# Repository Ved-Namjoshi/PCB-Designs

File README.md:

# PCB Designs – Embedded & Electronics Hardware

This repository contains PCB designs created using KiCad for embedded
and electronics hardware projects.

## Projects
- Tiny Solar Power Supply
- LMR51450 Buck Converter
- LED Torch Circuit
- Breadboard Power Supply

## Author
Ved Namjoshi

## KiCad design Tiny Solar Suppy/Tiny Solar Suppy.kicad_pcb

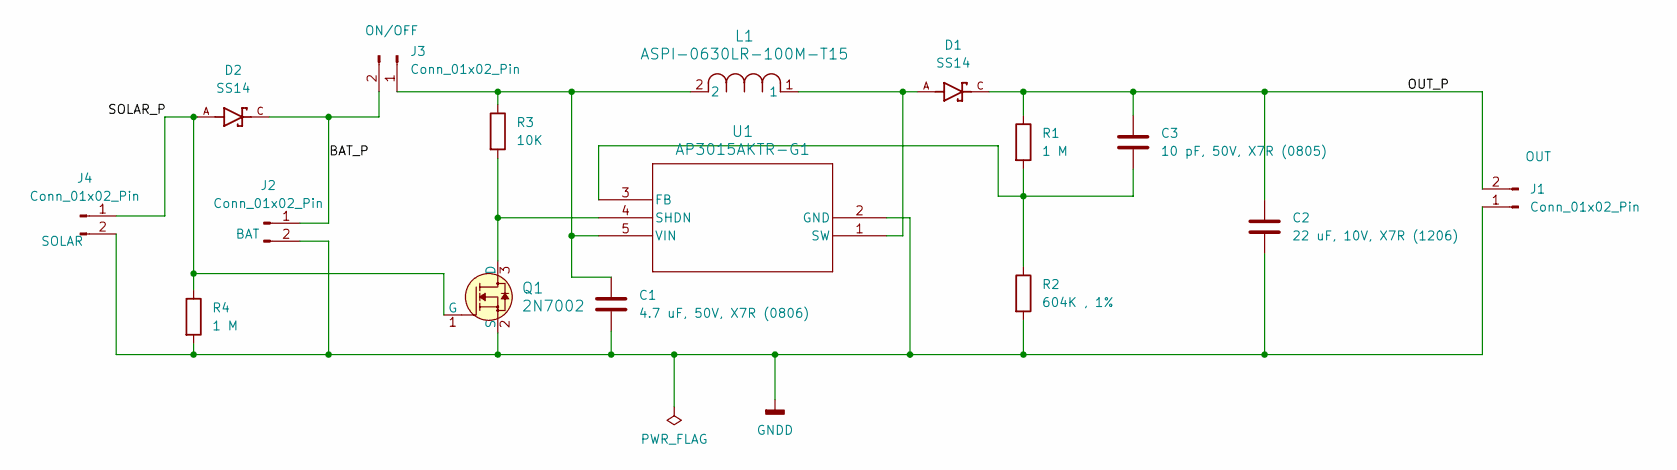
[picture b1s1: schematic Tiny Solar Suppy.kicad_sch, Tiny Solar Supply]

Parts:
C1: 4.7 uF, 50V, X7R (0806); C_0805_2012Metric
C2: 22 uF, 10V, X7R (1206); C_1206_3216Metric
C3: 10 pF, 50V, X7R (0805); C_0805_2012Metric
D1, D2: SS14; DIOM4325X250N; PARTREV O2102
J1, J2, J3: Conn_01x02_Pin; PinHeader_1x02_P2.54mm_Vertical
J4: Conn_01x02_Pin; PinHeader_1x02_P2.54mm_Horizontal
L1: ASPI-0630LR-100M-T15; IND_ASPI-0630LR_ABR
Q1: 2N7002; SOT-23-3; MPN 2N7002; Digi-Key_PN 2N7002NCT-ND
R1, R4: 1 M; R_0805_2012Metric
R2: 604K , 1%; R_0805_2012Metric
R3: 10K; R_0805_2012Metric
U1: AP3015AKTR-G1; SOT23-5_1P55X2P9_DIO

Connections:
/BAT_P: D2.C, J2.1, J3.2
/OUT_P: C2.1, C3.1, D1.C, J1.2, R1.1
/SOLAR_P: D2.A, J4.1, Q1.1 (G), R4.1
GNDD: C1.2, C2.2, J1.1, J2.2, J4.2, Q1.2 (S), R2.2, R4.2, U1.2 (GND)
unnamed: C1.1, J3.1, L1.2, R3.1, U1.5 (VIN)
unnamed: Q1.3 (D), R3.2, U1.4 (SHDN)
unnamed: C3.2, R1.2, R2.1, U1.3 (FB)
unnamed: D1.A, L1.1, U1.1 (SW)

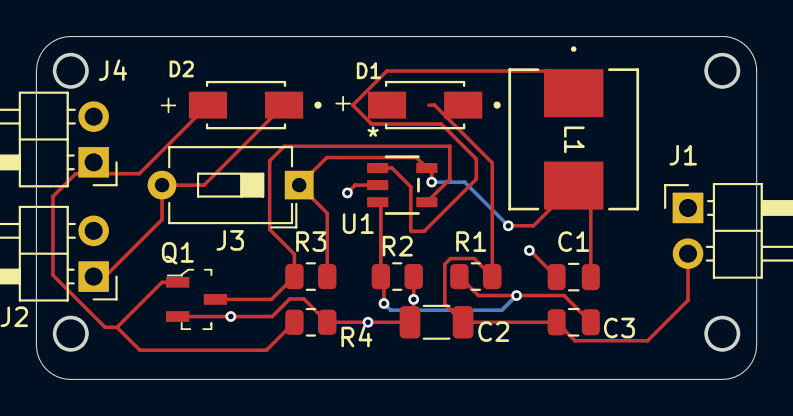
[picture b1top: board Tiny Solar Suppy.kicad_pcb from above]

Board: 2 copper layers, 40.0 x 19.1 mm, 16 parts (0 on the bottom side), 8 nets.

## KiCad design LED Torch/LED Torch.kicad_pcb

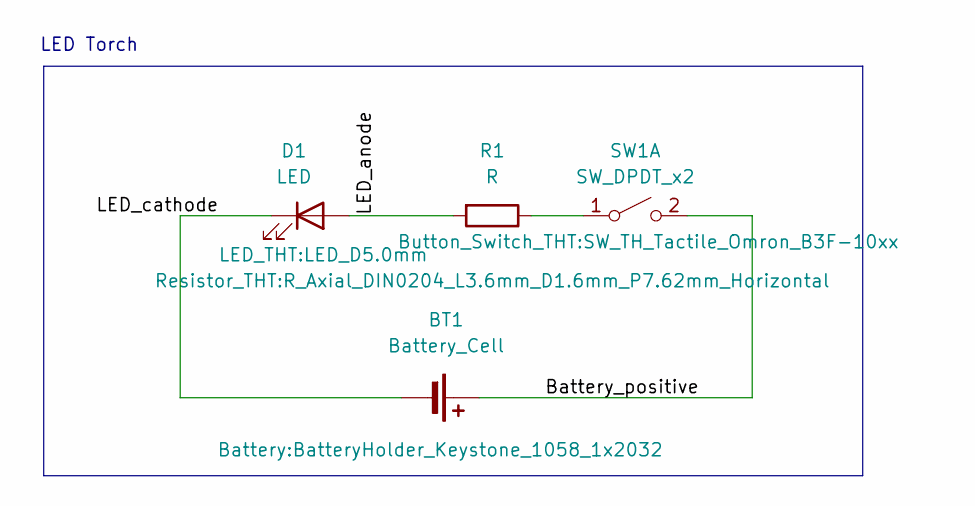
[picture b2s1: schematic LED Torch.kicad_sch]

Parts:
BT1: Battery_Cell; BatteryHolder_Keystone_1058_1x2032
D1: LED; LED_D5.0mm
R1: R; R_Axial_DIN0204_L3.6mm_D1.6mm_P7.62mm_Horizontal
SW1: SW_DPDT_x2; SW_TH_Tactile_Omron_B3F-10xx

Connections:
/Battery_positive: BT1.1 (+), SW1.2 (B)
/LED_anode: D1.2 (A), R1.2
/LED_cathode: BT1.2 (-), D1.1 (K)
unnamed: R1.1, SW1.1 (A)

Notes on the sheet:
LED Torch

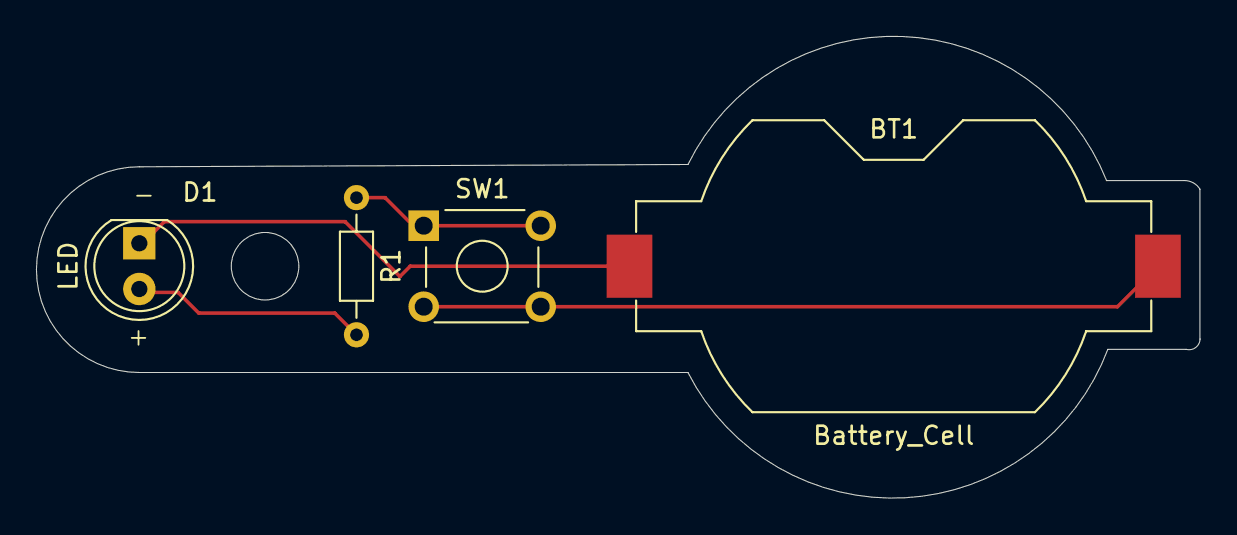
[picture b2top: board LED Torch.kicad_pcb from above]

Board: 2 copper layers, 64.6 x 25.6 mm, 4 parts (0 on the bottom side), 4 nets.

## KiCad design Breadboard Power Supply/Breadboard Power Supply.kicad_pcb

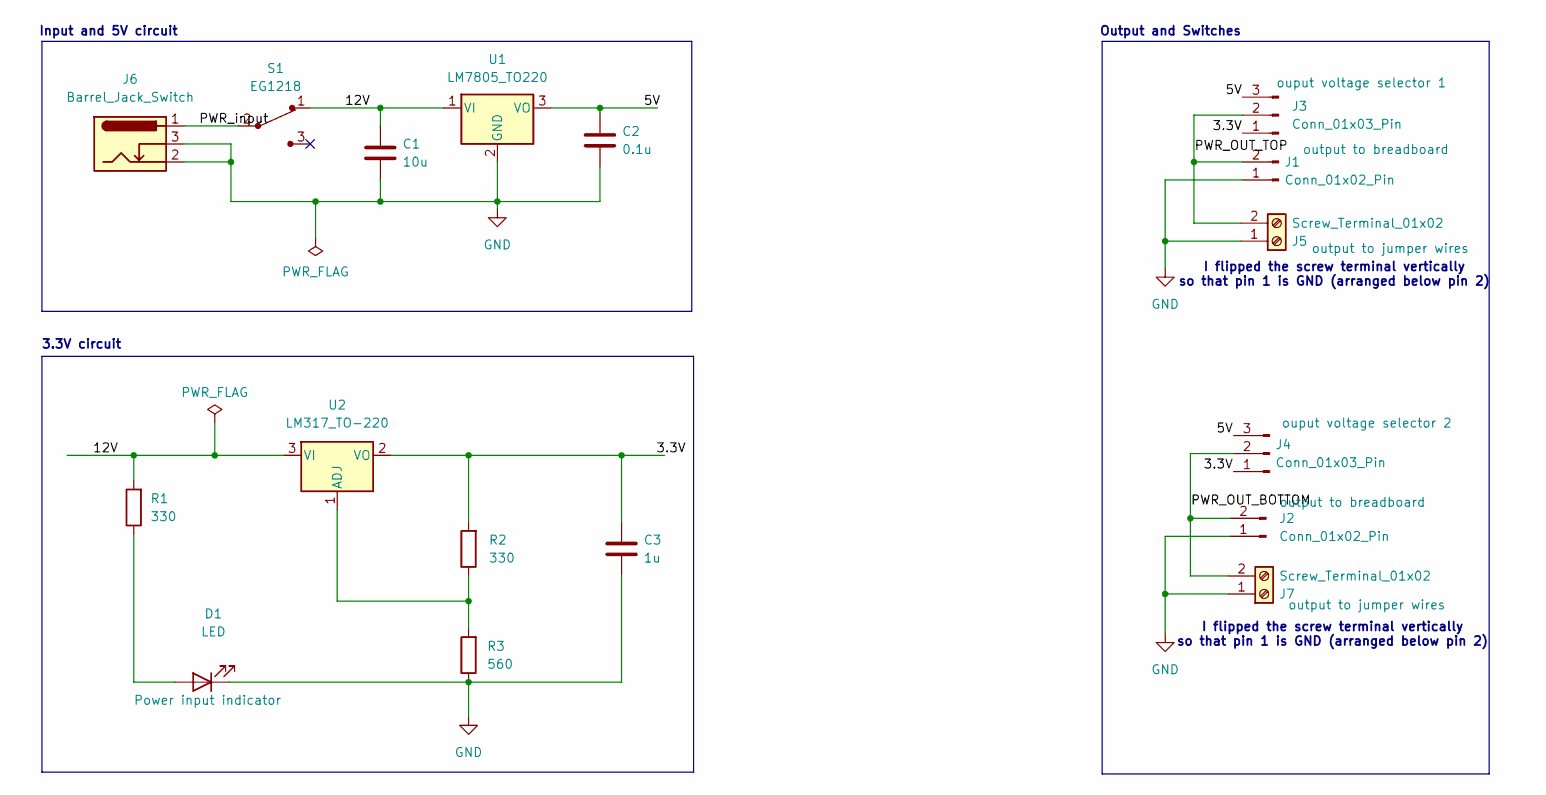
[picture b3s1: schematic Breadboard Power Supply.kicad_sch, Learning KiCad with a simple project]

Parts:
C1: 10u; C_Disc_D3.0mm_W1.6mm_P2.50mm
C2: 0.1u; C_Disc_D3.0mm_W1.6mm_P2.50mm
C3: 1u; C_Disc_D3.0mm_W1.6mm_P2.50mm
D1: LED; LED_D5.0mm
J1, J2: Conn_01x02_Pin; PinHeader_1x02_P2.54mm_Vertical
J3, J4: Conn_01x03_Pin; PinHeader_1x03_P2.54mm_Vertical
J5, J7: Screw_Terminal_01x02; TerminalBlock_bornier-2_P5.08mm
J6: Barrel_Jack_Switch; BarrelJack_Horizontal
R1, R2: 330; R_Axial_DIN0204_L3.6mm_D1.6mm_P7.62mm_Horizontal
R3: 560; R_Axial_DIN0204_L3.6mm_D1.6mm_P7.62mm_Horizontal
S1: EG1218; Switch_Slide_11.6x4mm_EG1218; MPN EG1218; Digi-Key_PN EG1903-ND
U1: LM7805_TO220; TO-220-3_Vertical
U2: LM317_TO-220; TO-220-3_Vertical

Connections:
/3.3V: C3.1, J3.1, J4.1, R2.2, U2.2 (VO)
/5V: C2.1, J3.3, J4.3, U1.3 (VO)
/12V: C1.1, R1.2, S1.1, U1.1 (VI), U2.3 (VI)
/PWR_OUT_BOTTOM: J2.2, J4.2, J7.2
/PWR_OUT_TOP: J1.2, J3.2, J5.2
/PWR_input: J6.1, S1.2
GND: C1.2, C2.2, C3.2, D1.1 (K), J1.1, J2.1, J5.1, J6.2, J6.3, J7.1, R3.1, U1.2 (GND)
unnamed: D1.2 (A), R1.1
unnamed: R2.1, R3.2, U2.1 (ADJ)

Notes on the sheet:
I flipped the screw terminal vertically so that pin 1 is GND (arranged below pin 2)
Input and 5V circuit
3.3V circuit
Output and Switches

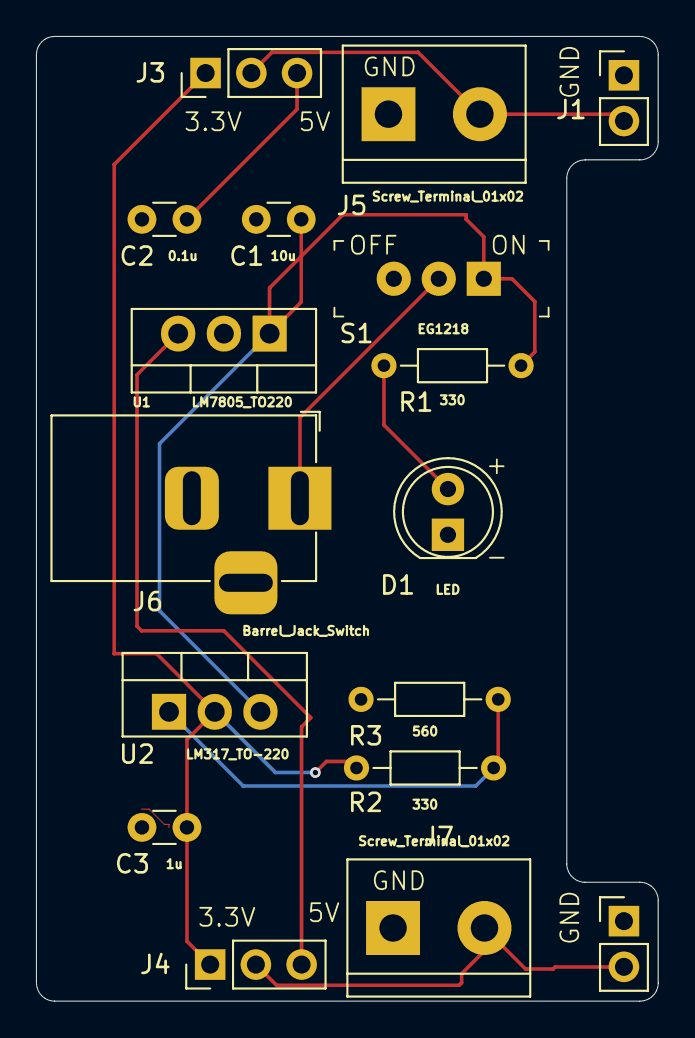
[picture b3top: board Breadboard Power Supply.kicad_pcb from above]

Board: 2 copper layers, 34.5 x 53.6 mm, 17 parts (0 on the bottom side), 9 nets.

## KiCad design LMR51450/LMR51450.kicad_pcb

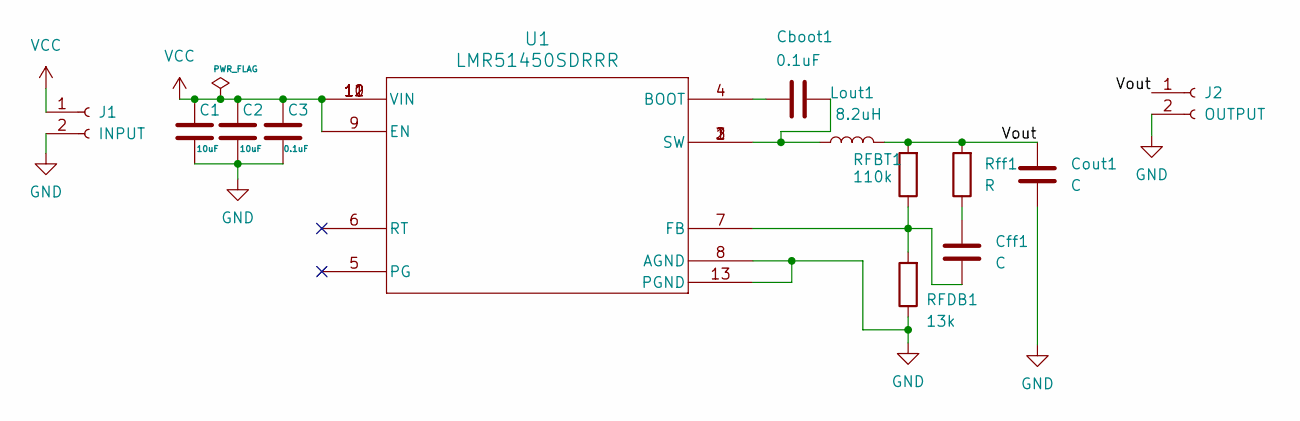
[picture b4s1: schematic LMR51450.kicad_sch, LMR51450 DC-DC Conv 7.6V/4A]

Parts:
C1, C2: 10uF; C_0805_2012Metric_Pad1.18x1.45mm_HandSolder
C3: 0.1uF; C_0805_2012Metric_Pad1.18x1.45mm_HandSolder
Cboot1: 0.1uF; C_0805_2012Metric_Pad1.18x1.45mm_HandSolder
Cff1: C; C_0805_2012Metric_Pad1.18x1.45mm_HandSolder
Cout1: C; C_1808_4520Metric_Pad1.72x2.30mm_HandSolder
J1: INPUT; TerminalBlock_Phoenix_MKDS-1,5-2-5.08_1x02_P5.08mm_Horizont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
J2: OUTPUT; TerminalBlock_Phoenix_MKDS-1,5-2-5.08_1x02_P5.08mm_Horizont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
Lout1: 8.2uH; L_Axial_L11.0mm_D4.5mm_P15.24mm_Horizontal_Fastron_MECC
RFBT1: 110k; R_0805_2012Metric_Pad1.20x1.40mm_HandSolder
RFDB1: 13k; R_0805_2012Metric_Pad1.20x1.40mm_HandSolder
Rff1: R; R_0805_2012Metric_Pad1.20x1.40mm_HandSolder
U1: LMR51450SDRRR; WSON_SDRRR_TEX

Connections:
/Vout: Cout1.2, J2.1, Lout1.2, RFBT1.2, Rff1.2
GND: C1.1, C2.1, C3.1, Cout1.1, J1.2, J2.2, RFDB1.1, U1.8 (AGND), U1.13 (PGND)
unnamed: Cboot1.2, Lout1.1, U1.1 (SW), U1.2 (SW), U1.3 (SW)
unnamed: Cff1.2, Rff1.1
unnamed: Cboot1.1, U1.4 (BOOT)
unnamed: Cff1.1, RFBT1.1, RFDB1.2, U1.7 (FB)
VCC: C1.2, C2.2, C3.2, J1.1, U1.9 (EN), U1.10 (VIN), U1.11 (VIN), U1.12 (VIN)

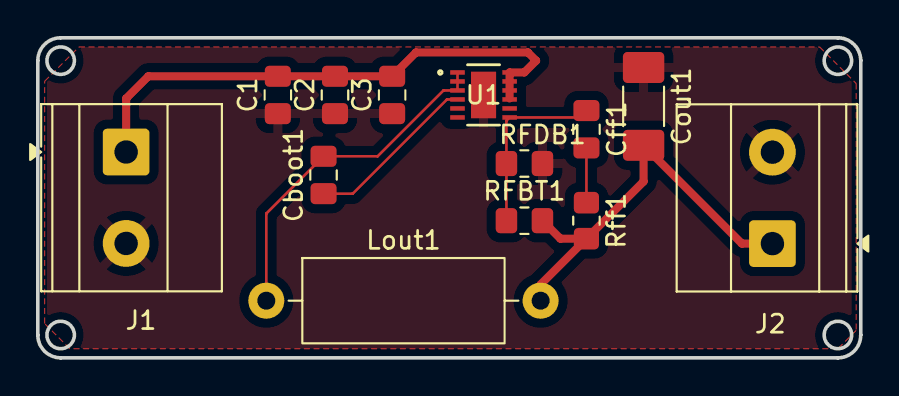
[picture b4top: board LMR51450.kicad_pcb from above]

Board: 2 copper layers, 45.7 x 17.8 mm, 13 parts (0 on the bottom side), 7 nets.

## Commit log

2026-01-20 Initial commit: PCB designs
